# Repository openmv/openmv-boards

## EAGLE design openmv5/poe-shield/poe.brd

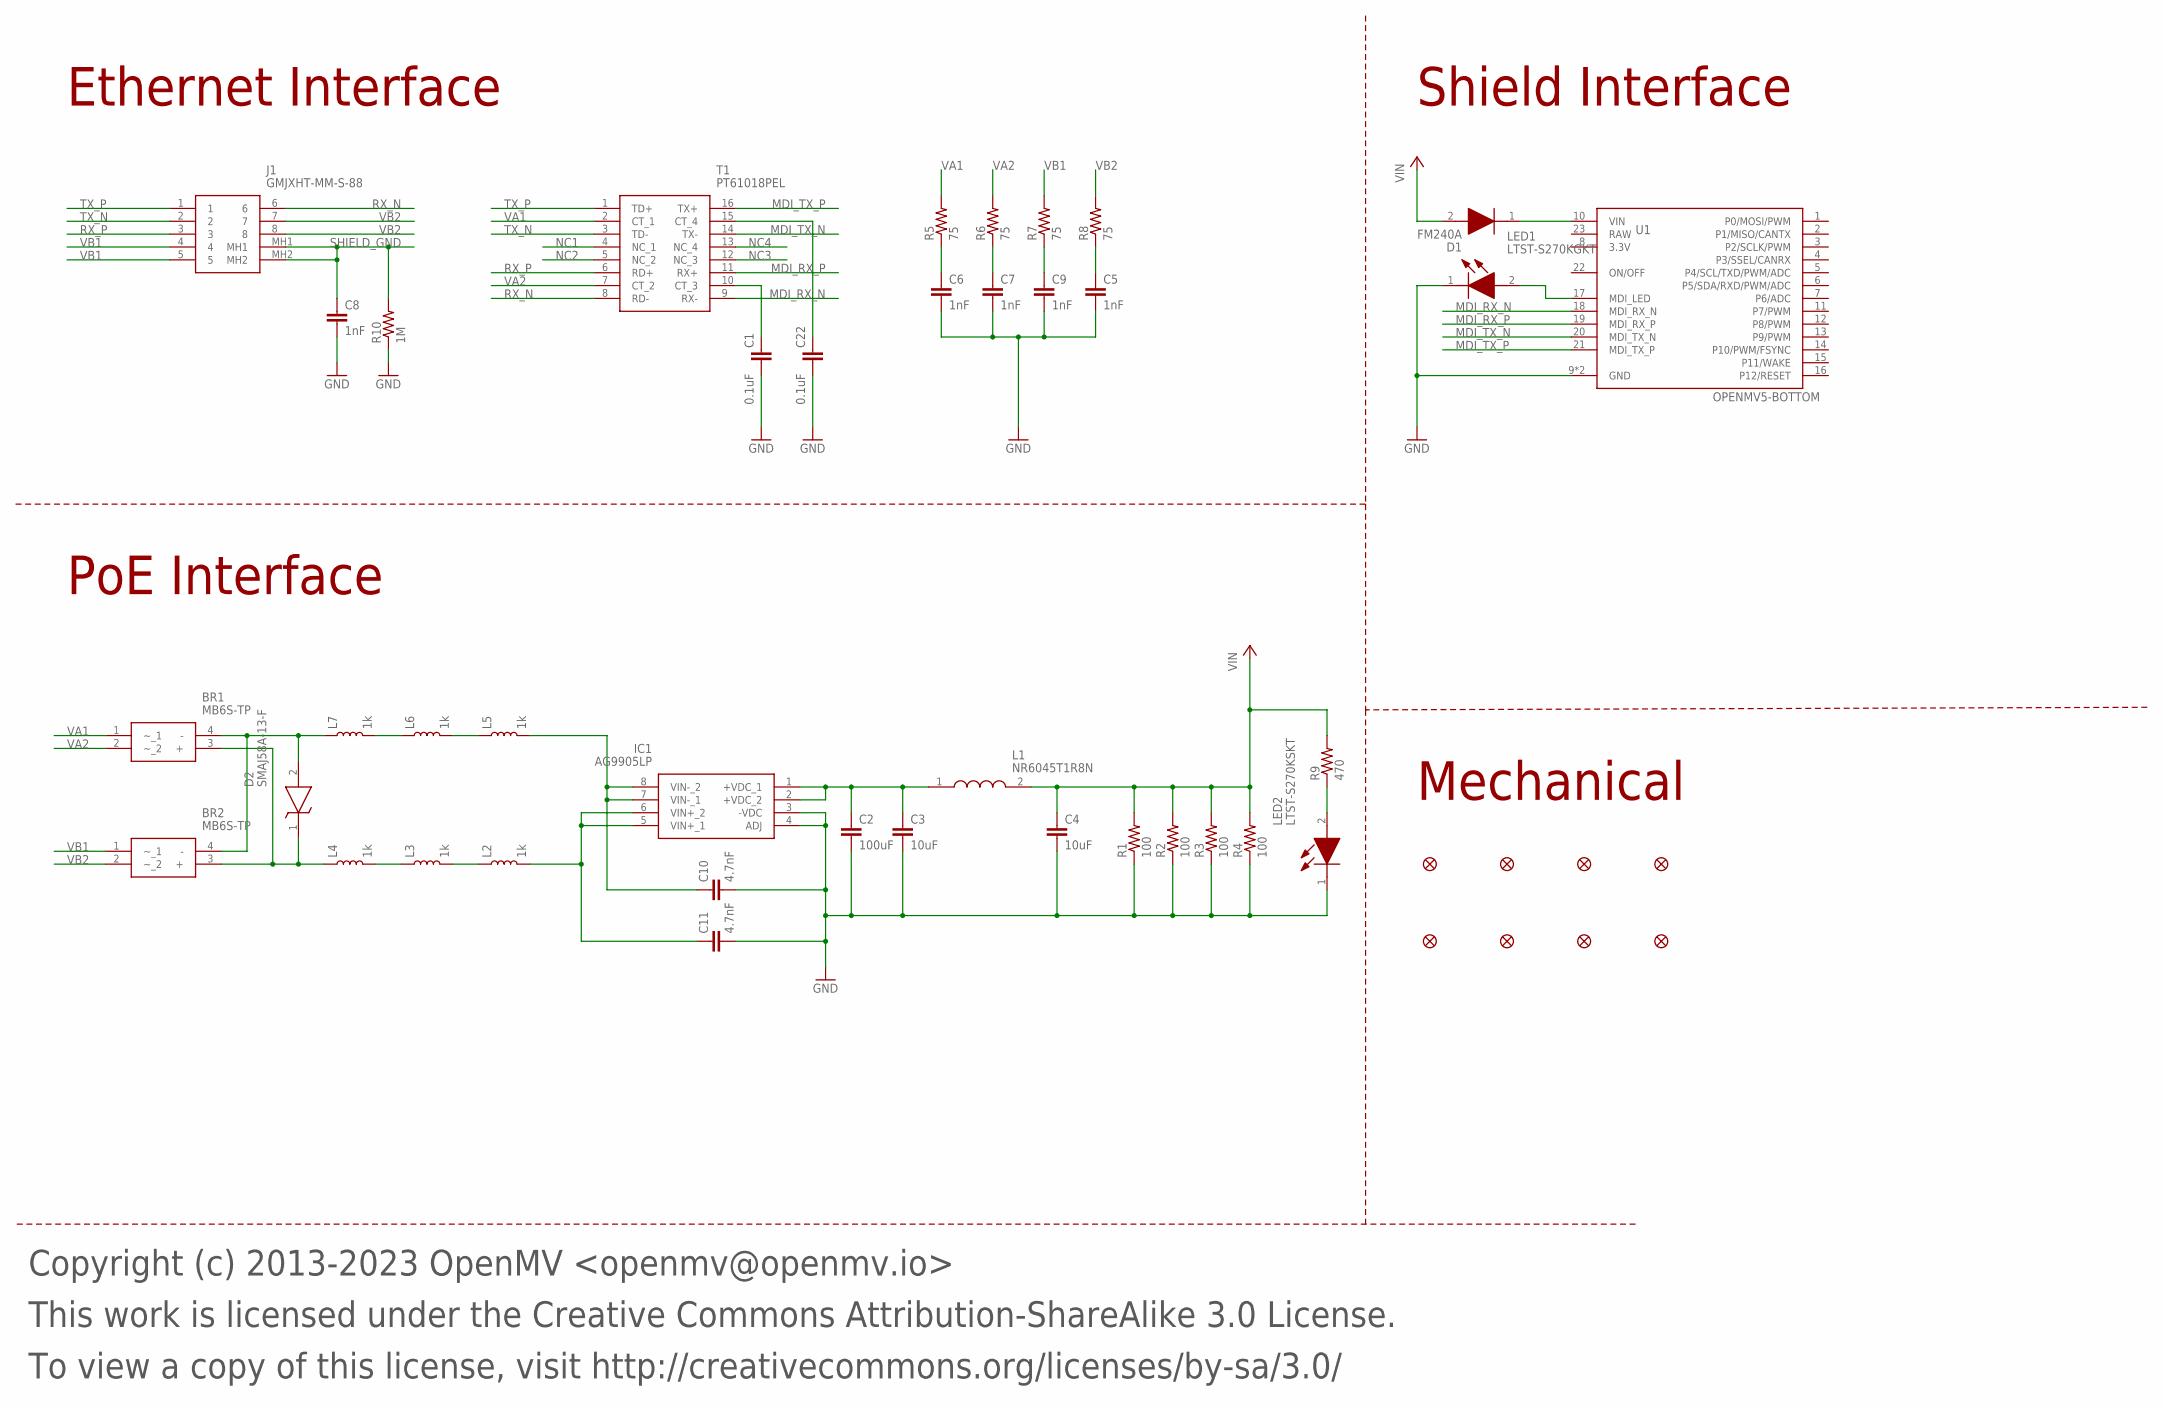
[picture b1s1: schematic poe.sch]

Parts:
BR1, BR2: MB6S-TP; SOP254P665X270-4N; MPN MB6S-TP
C1, C22: 0.1uF; C0201; MPN CL03A104KQ3NNNC
C2: 100uF; C1206; MPN CL31A107MQHNNWE
C3, C4: 10uF; C0402; MPN GRM155R60J106ME05D
C5, C6, C7, C8, C9: 1nF; C1206; MPN 1206B102K252CT
C10, C11: 4.7nF; C1812; MPN 202S43W472KV4E
D1: FM240A; DIOM5025X231N; MPN FM240A
D2: SMAJ58A-13-F; DIOM5226X230N; MPN SMAJ58A/TR13
FD1, FD2, FD3, FD4, FD5, FD6, FD7, FD8: FIDUCIAL1X2; FIDUCIAL-1X2
IC1: AG9905LP; MPN Ag9905LP
J1: GMJXHT-MM-S-88; GMJXHTMMS88; MPN GMJXHT-MM-S-88
L1: NR6045T1R8N; MPN NR6045T1R8N
L2, L3, L4, L5, L6, L7: 1k; 0402; MPN BBPY00100505102Y00
LED1: LTST-S270KGKT; LTSTS270K; MPN LTST-S270KGKT
LED2: LTST-S270KSKT; LTSTS270K; MPN LTST-S270KSKT
R1, R2, R3, R4: 100; R2512; MPN RC2512JK-07100RL
R5, R6, R7, R8: 75; R0402; MPN 0402WGF750JTCE
R9: 470; R0603; MPN 0603WAJ0471T5E
R10: 1M; R1206; MPN RMCF1206FT1M00
T1: PT61018PEL; SOIC127P930X565-16N; MPN PT61018PEL
U1: OPENMV5-BOTTOM

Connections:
GND: C1.2, C2.2, C3.2, C4.2, C5.2, C6.2, C7.2, C8.2, C9.2, C10.2, C11.2, C22.2, IC1.3 (-VDC), IC1.4 (ADJ), LED1.1 (K), LED2.1 (K), R1.1, R2.1, R3.1, R4.1, R10.1, U1.9 (GND), U1.24 (GND)
MDI_LED: LED1.2 (A), U1.17 (MDI_LED)
MDI_RX_CT: C1.1, T1.10 (CT_3)
MDI_RX_N: T1.9 (RX-), U1.18 (MDI_RX_N)
MDI_RX_P: T1.11 (RX+), U1.19 (MDI_RX_P)
MDI_TX_CT: C22.1, T1.15 (CT_4)
MDI_TX_N: T1.14 (TX-), U1.20 (MDI_TX_N)
MDI_TX_P: T1.16 (TX+), U1.21 (MDI_TX_P)
NC1: T1.4 (NC_1)
NC2: T1.5 (NC_2)
NC3: T1.12 (NC_3)
NC4: T1.13 (NC_4)
POE_VIN_INT_N: C10.1, IC1.7 (VIN-_1), IC1.8 (VIN-_2), L5.2
POE_VIN_INT_P: C11.1, IC1.5 (VIN+_1), IC1.6 (VIN+_2), L2.2
POE_VIN_N: BR1.4 (-), BR2.4 (-), D2.2 (A), L7.1
POE_VIN_N0: L6.1, L7.2
POE_VIN_N1: L5.1, L6.2
POE_VIN_P: BR1.3 (+), BR2.3 (+), D2.1 (K), L4.1
POE_VIN_P0: L3.1, L4.2
POE_VIN_P1: L2.1, L3.2
RX_N: J1.6, T1.8 (RD-)
RX_P: J1.3, T1.6 (RD+)
SHIELD_GND: C8.1, J1.MH1, J1.MH2, R10.2
TX_N: J1.2, T1.3 (TD-)
TX_P: J1.1, T1.1 (TD+)
VA1: BR1.1 (~_1), R5.2, T1.2 (CT_1)
VA1_ISO: C6.1, R5.1
VA2: BR1.2 (~_2), R6.2, T1.7 (CT_2)
VA2_ISO: C7.1, R6.1
VB1: BR2.1 (~_1), J1.4, J1.5, R7.2
VB1_ISO: C9.1, R7.1
VB2: BR2.2 (~_2), J1.7, J1.8, R8.2
VB2_ISO: C5.1, R8.1
VDC: C2.1, C3.1, IC1.1 (+VDC_1), IC1.2 (+VDC_2), L1.1
VIN: C4.1, D1.2 (A), L1.2, R1.2, R2.2, R3.2, R4.2, R9.2
VIN_INT: D1.1 (K), U1.10 (VIN)
VIN_LED: LED2.2 (A), R9.1

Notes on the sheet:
Copyright (c) 2013-2023 OpenMV <openmv@openmv.io>
This work is licensed under the Creative Commons Attribution-ShareAlike 3.0 License.
To view a copy of this license, visit http://creativecommons.org/licenses/by-sa/3.0/
Ethernet Interface
PoE Interface
Shield Interface
Mechanical

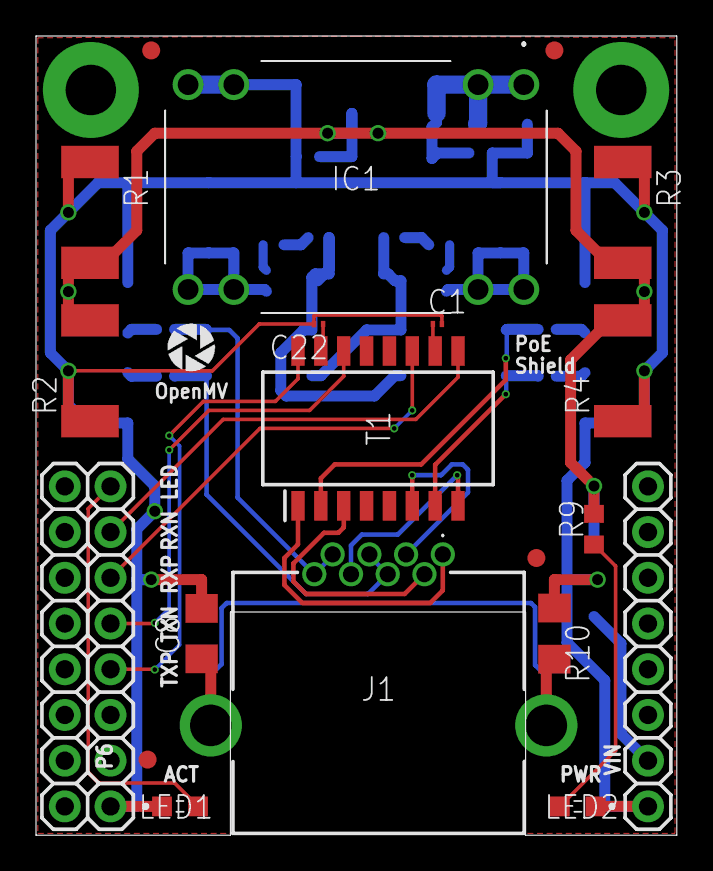
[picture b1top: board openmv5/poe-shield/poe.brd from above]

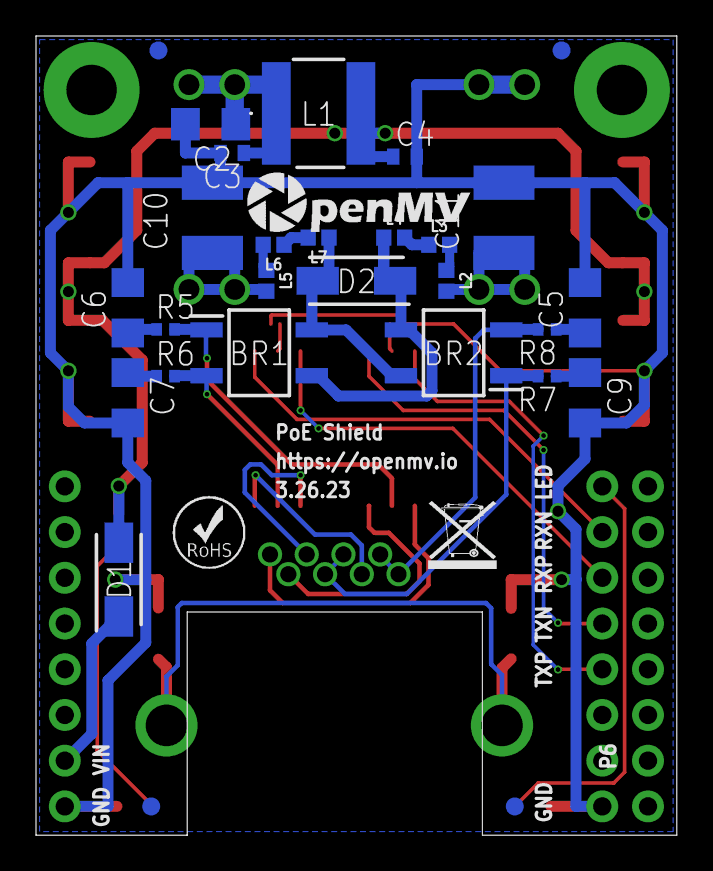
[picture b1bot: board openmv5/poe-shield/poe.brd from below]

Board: 2 copper layers, 35.6 x 44.4 mm, 51 parts (31 on the bottom side), 33 nets.

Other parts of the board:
U$1: WEEE
U$2: ROHS
U$3: OMV-LOGO
U$9: OPENMV-LOGO

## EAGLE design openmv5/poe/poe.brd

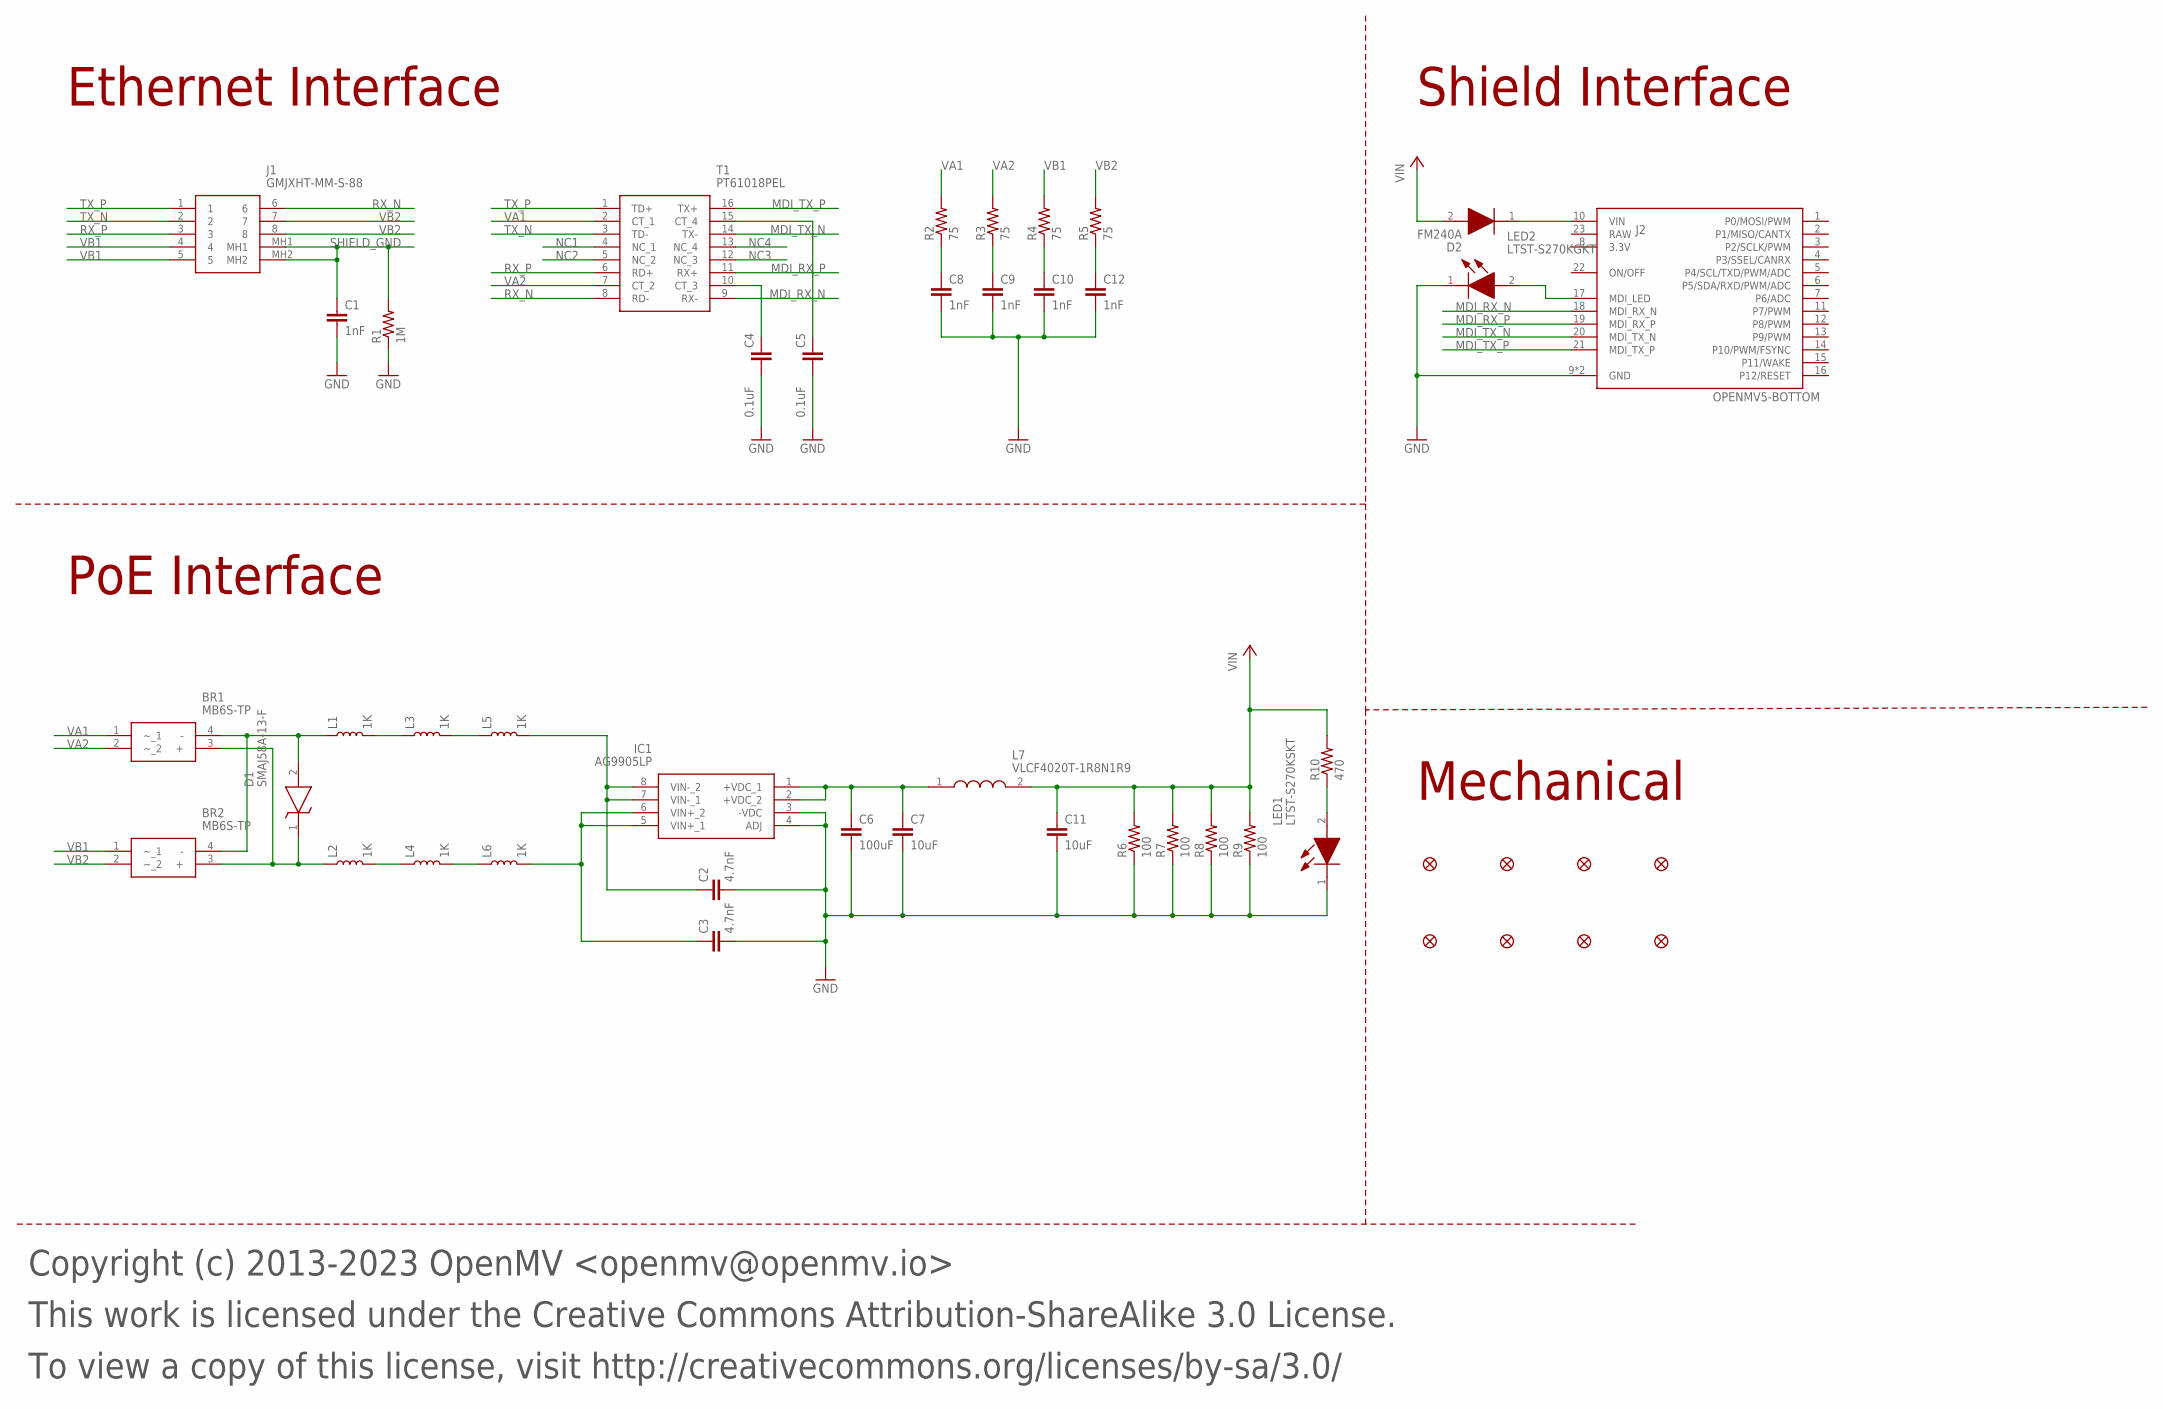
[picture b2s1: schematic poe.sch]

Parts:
BR1, BR2: MB6S-TP; SOP254P665X270-4N; MPN MB6S-TP
C1, C8, C9, C10, C12: 1nF; C1206; MPN 1206B102K252CT
C2, C3: 4.7nF; C1812; MPN 202S43W472KV4E
C4, C5: 0.1uF; 0402; MPN GRM155R71H104KE14D
C6: 100uF; C1206; MPN CL31A107MQHNNWE
C7, C11: 10uF; C0402; MPN GRM155R60J106ME05D
D1: SMAJ58A-13-F; DIOM5226X230N; MPN SMAJ58A/TR13
D2: FM240A; DIOM5025X231N; MPN FM240A
FD1, FD2, FD3, FD4, FD5, FD6, FD7, FD8: FIDUCIAL1X2; FIDUCIAL-1X2
IC1: AG9905LP; MPN Ag9905LP
J1: GMJXHT-MM-S-88; GMJXHTMMS88; MPN GMJXHT-MM-S-88
J2: OPENMV5-BOTTOM
L1, L2, L3, L4, L5, L6: 1K; 0805; MPN BBPY00100505102Y00
L7: VLCF4020T-1R8N1R9; VLCF4020; MPN VLCF4020T-1R8N1R9
LED1: LTST-S270KSKT; LTSTS270K; MPN LTST-S270KSKT
LED2: LTST-S270KGKT; LTSTS270K; MPN LTST-S270KGKT
R1: 1M; R1206; MPN RMCF1206FT1M00
R2, R3, R4, R5: 75; R0402; MPN CR0402-FX-75R0GLF
R6, R7, R8, R9: 100; R2512; MPN RC2512JK-07100RL
R10: 470; R0603; MPN CR0603-FX-4700ELF
T1: PT61018PEL; SOIC127P930X565-16N; MPN PT61018PEL

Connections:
GND: C1.2, C2.2, C3.2, C4.2, C5.2, C6.2, C7.2, C8.2, C9.2, C10.2, C11.2, C12.2, IC1.3 (-VDC), IC1.4 (ADJ), J2.9 (GND), J2.24 (GND), LED1.1 (K), LED2.1 (K), R1.1, R6.1, R7.1, R8.1, R9.1
MDI_LED: J2.17 (MDI_LED), LED2.2 (A)
MDI_RX_CT: C4.1, T1.10 (CT_3)
MDI_RX_N: J2.18 (MDI_RX_N), T1.9 (RX-)
MDI_RX_P: J2.19 (MDI_RX_P), T1.11 (RX+)
MDI_TX_CT: C5.1, T1.15 (CT_4)
MDI_TX_N: J2.20 (MDI_TX_N), T1.14 (TX-)
MDI_TX_P: J2.21 (MDI_TX_P), T1.16 (TX+)
NC1: T1.4 (NC_1)
NC2: T1.5 (NC_2)
NC3: T1.12 (NC_3)
NC4: T1.13 (NC_4)
POE_VIN_INT_N: C2.1, IC1.7 (VIN-_1), IC1.8 (VIN-_2), L5.2
POE_VIN_INT_P: C3.1, IC1.5 (VIN+_1), IC1.6 (VIN+_2), L6.2
POE_VIN_N: BR1.4 (-), BR2.4 (-), D1.2 (A), L1.1
POE_VIN_N0: L1.2, L3.1
POE_VIN_N1: L3.2, L5.1
POE_VIN_P: BR1.3 (+), BR2.3 (+), D1.1 (K), L2.1
POE_VIN_P0: L2.2, L4.1
POE_VIN_P1: L4.2, L6.1
RX_N: J1.6, T1.8 (RD-)
RX_P: J1.3, T1.6 (RD+)
SHIELD_GND: C1.1, J1.MH1, J1.MH2, R1.2
TX_N: J1.2, T1.3 (TD-)
TX_P: J1.1, T1.1 (TD+)
VA1: BR1.1 (~_1), R2.2, T1.2 (CT_1)
VA1_ISO: C8.1, R2.1
VA2: BR1.2 (~_2), R3.2, T1.7 (CT_2)
VA2_ISO: C9.1, R3.1
VB1: BR2.1 (~_1), J1.4, J1.5, R4.2
VB1_ISO: C10.1, R4.1
VB2: BR2.2 (~_2), J1.7, J1.8, R5.2
VB2_ISO: C12.1, R5.1
VDC: C6.1, C7.1, IC1.1 (+VDC_1), IC1.2 (+VDC_2), L7.1
VIN: C11.1, D2.2 (A), L7.2, R6.2, R7.2, R8.2, R9.2, R10.2
VIN_INT: D2.1 (K), J2.10 (VIN)
VIN_LED: LED1.2 (A), R10.1

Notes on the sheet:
Copyright (c) 2013-2023 OpenMV <openmv@openmv.io>
This work is licensed under the Creative Commons Attribution-ShareAlike 3.0 License.
To view a copy of this license, visit http://creativecommons.org/licenses/by-sa/3.0/
Ethernet Interface
PoE Interface
Shield Interface
Mechanical

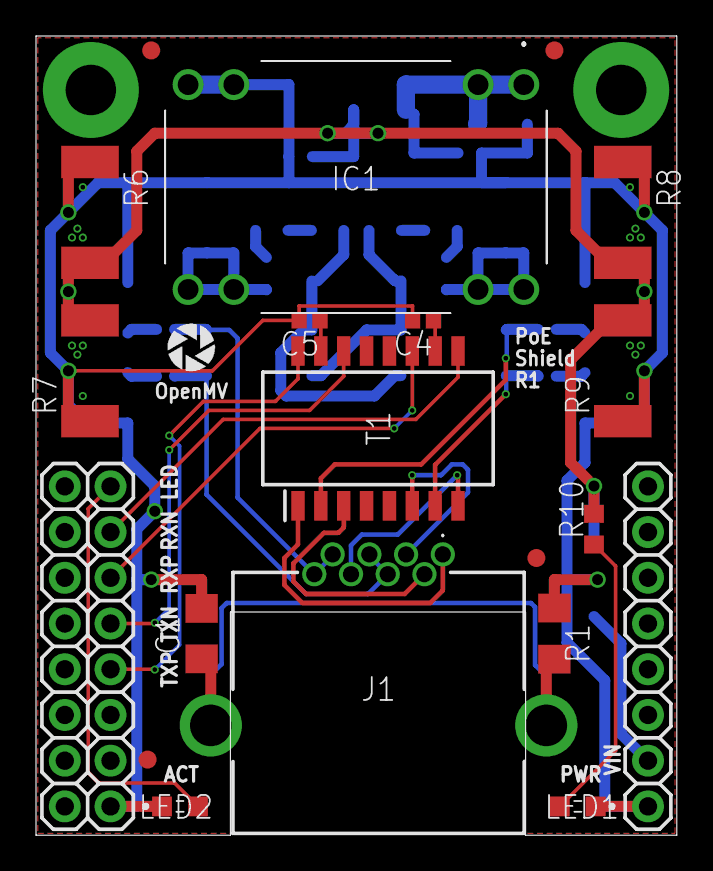
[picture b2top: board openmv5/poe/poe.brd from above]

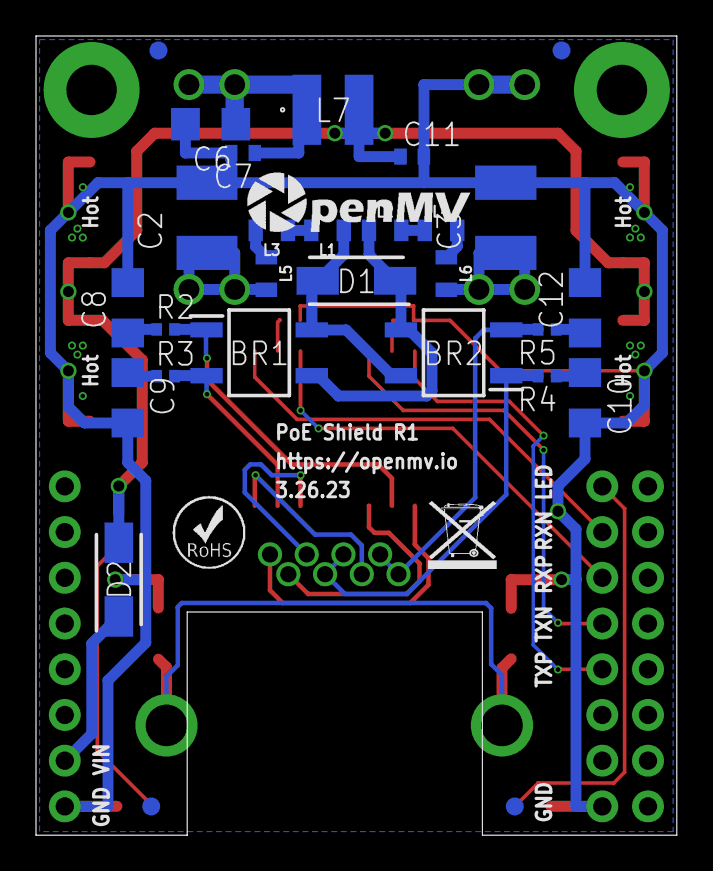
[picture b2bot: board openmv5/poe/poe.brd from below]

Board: 2 copper layers, 35.6 x 44.4 mm, 51 parts (31 on the bottom side), 33 nets.

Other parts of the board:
U$1: WEEE
U$2: ROHS
U$3: OMV-LOGO
U$9: OPENMV-LOGO

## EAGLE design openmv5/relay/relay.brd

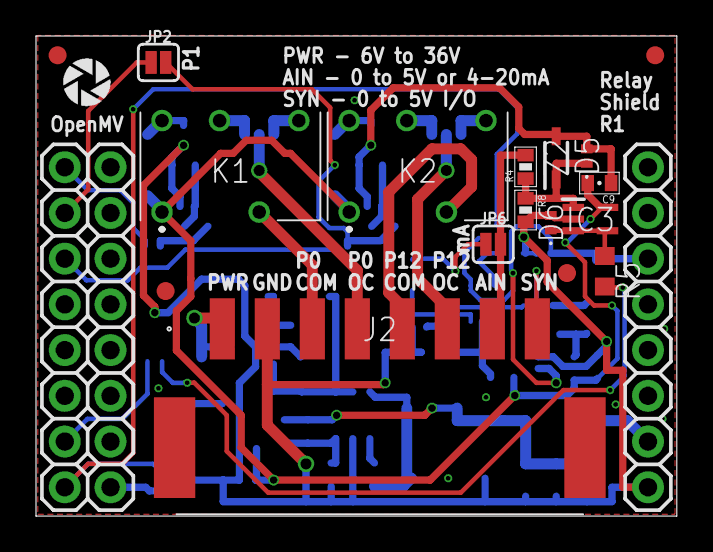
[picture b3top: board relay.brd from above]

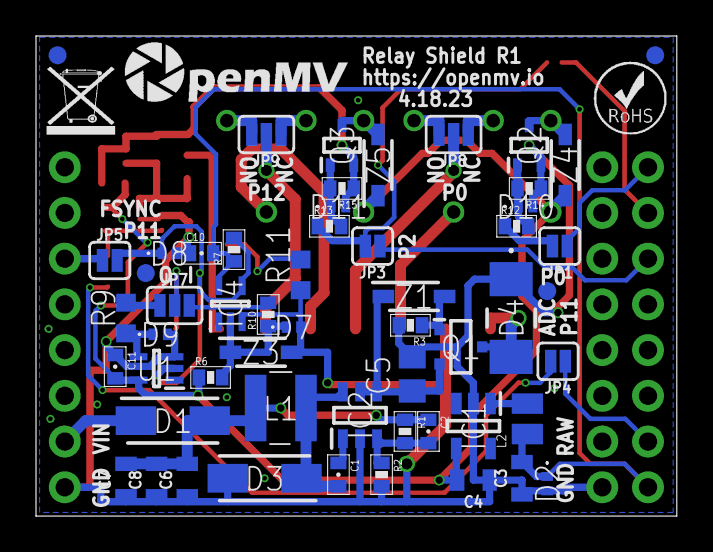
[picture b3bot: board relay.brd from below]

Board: 2 copper layers, 35.6 x 26.7 mm, 77 parts (58 on the bottom side), 42 nets.

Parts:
C1, C9, C10, C11: 0.1uF; 0402-CAP
C2: 100pF; 0402-CAP
C3, C4, C6, C7, C8: 22uF; 0805
C5: 10uF; C0805
D1, D3: FM240A; DIOM5025X231N
D2, D5, D6, D7, D8, D9, D10, D11: CPDQT5V0HE-HF; CPDQT5V0HEHF
D4: SMAJ40CAE3_TR13; SMAJ40CAE3TR13
FD1, FD2, FD3, FD4, FD5, FD6, FD7, FD8: FIDUCIAL1X2; FIDUCIAL-1X2
IC1: TPS613222ADBVR; SOT95P280X145-5N
IC2: AP64060WU-7; SOT95P280X100-6N
IC3: LM321LVIDCKR; SOT65P210X110-5N
IC4: 74LVC1G07GW,125; SOT65P212X110-5N
J1: OPENMV5-TOP
J2: 1771088
JP1, JP3, JP4, JP5: JUMPER-SMT_2_NC_PASTE_SILK; SMT-JUMPER_2_NC_PASTE_SILK
JP2, JP6: JUMPER-SMT_2_NO_SILK; SMT-JUMPER_2_NO_SILK
JP7, JP8, JP9: JUMPER-SMT_3_1-NC_PASTE_SILK; SMT-JUMPER_3_1-NC_PASTE_SILK
K1, K2: IMC03TS
L1: NRS4018T100MDGJ
L2: MAKK2016T2R2M; INDC2016X100N
Q1: SSM3J356R,LF; SOTFL95P240X88-3N
Q2, Q3: 2N7002KW_R1_00001; SOT65P210X110-3N
R1: 133K; 0402-RES
R2: 22.1K; 0402-RES
R3, R6, R7, R8, R14, R15: 100K; 0402-RES
R4: 51K; 0402-RES
R5, R9: 470; R0603
R10, R12, R13: 10K; 0402-RES
R11: 240; R0603
U1: 74LVC1G17SE-7; SOT65P210X110-5N
U$1: WEEE
U$2: ROHS
U$3: OMV-LOGO
U$9: OPENMV-LOGO
Z1, Z3, Z4, Z5: MMSZ5231B-7-F; SOD3716X145N
Z2: MM3Z3V6T1G; SOD2512X110N

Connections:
AIN: J2.7, JP6.2, R4.2
AIN_INT: D5.1, IC3.1, R4.1, R8.1, Z2.1
AIN_OUT: D6.1, IC3.3, IC3.4, R5.1
AIN_S: JP6.1, R11.2
EXT_VIN: D4.2, J2.1, Q1.3
EXT_VIN_BST: C1.1, IC2.1
EXT_VIN_FB: C2.2, IC2.3, R1.2, R2.1
EXT_VIN_G: Q1.1, R3.1, Z1.2
EXT_VIN_INT: C5.1, IC2.4, IC2.5, Q1.2, Z1.1
EXT_VIN_OUT: C2.1, C6.2, C7.2, C8.2, D1.2, L1.2, R1.1
EXT_VIN_SW: C1.2, D3.1, IC2.6, L1.1
GND: C3.1, C4.1, C5.2, C6.1, C7.1, C8.1, C9.1, C10.1, C11.1, D2.2, D3.2, D4.1, D5.2, D6.2, D7.2, D8.2, D9.2, D10.2, D11.2, IC1.2, IC2.2, IC3.2, IC4.3, J1.9, J1.24, J2.2, Q2.2, Q3.2, R2.2, R3.2, R8.2, R11.1, R14.1, R15.1, U1.3, Z2.2, Z3.2
P0: JP1.2, R12.1
P0_COM: J2.3, K1.3
P0_CONTROL: D10.1, Q2.1, R12.2, R14.2
P0_INT: J1.1, JP1.1
P0_N: J2.4, JP8.2
P0_NC: JP8.1, K1.7
P0_NO: JP8.3, K1.5
P0_RELAY: K1.8, Q2.3, Z4.2
P1_INT: J1.2, JP2.1
P2_INT: J1.3, JP3.1
P6_ADC: JP4.2, R5.2
P6_ADC_INT: J1.7, JP4.1
P10_FSYNC: D8.1, IC4.4, JP5.2, R7.2, U1.2
P10_FSYNC_INT: J1.14, JP5.1
P12: JP2.2, JP3.2, R13.1
P12_COM: J2.5, K2.3
P12_CONTROL: D11.1, Q3.1, R13.2, R15.2
P12_N: J2.6, JP9.2
P12_NC: JP9.1, K2.7
P12_NO: JP9.3, K2.5
P12_RELAY: K2.8, Q3.3, Z5.2
SW: IC1.1, L2.2
SYNC: J2.8, JP7.2
SYNC_IN: JP7.3, R10.2
SYNC_IN_INT: D7.1, IC4.2, R6.2, R10.1, Z3.1
SYNC_OUT: JP7.1, R9.2
SYNC_OUT_INT: D9.1, R9.1, U1.4
VCC: C3.2, C10.2, D2.1, IC4.5, J1.8, L2.1, R7.1
VIN: D1.1, J1.10
V_BATT: C4.2, C9.2, C11.2, IC1.4, IC3.5, K1.1, K2.1, R6.1, U1.5, Z4.1, Z5.1

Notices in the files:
shields/rs232/rs232.sch:
Copyright (c) 2019 OpenMV LLC
This work is licensed under the Creative Commons Attribution-ShareAlike 4.0 License.
To view a copy of this license, visit http://creativecommons.org/licenses/by-sa/4.0
parts and their libraries:
SparkFun-Coils: Licensing: Creative Commons ShareAlike 4.0 International - https://creativecommons.org/licenses/by-sa/4.0
